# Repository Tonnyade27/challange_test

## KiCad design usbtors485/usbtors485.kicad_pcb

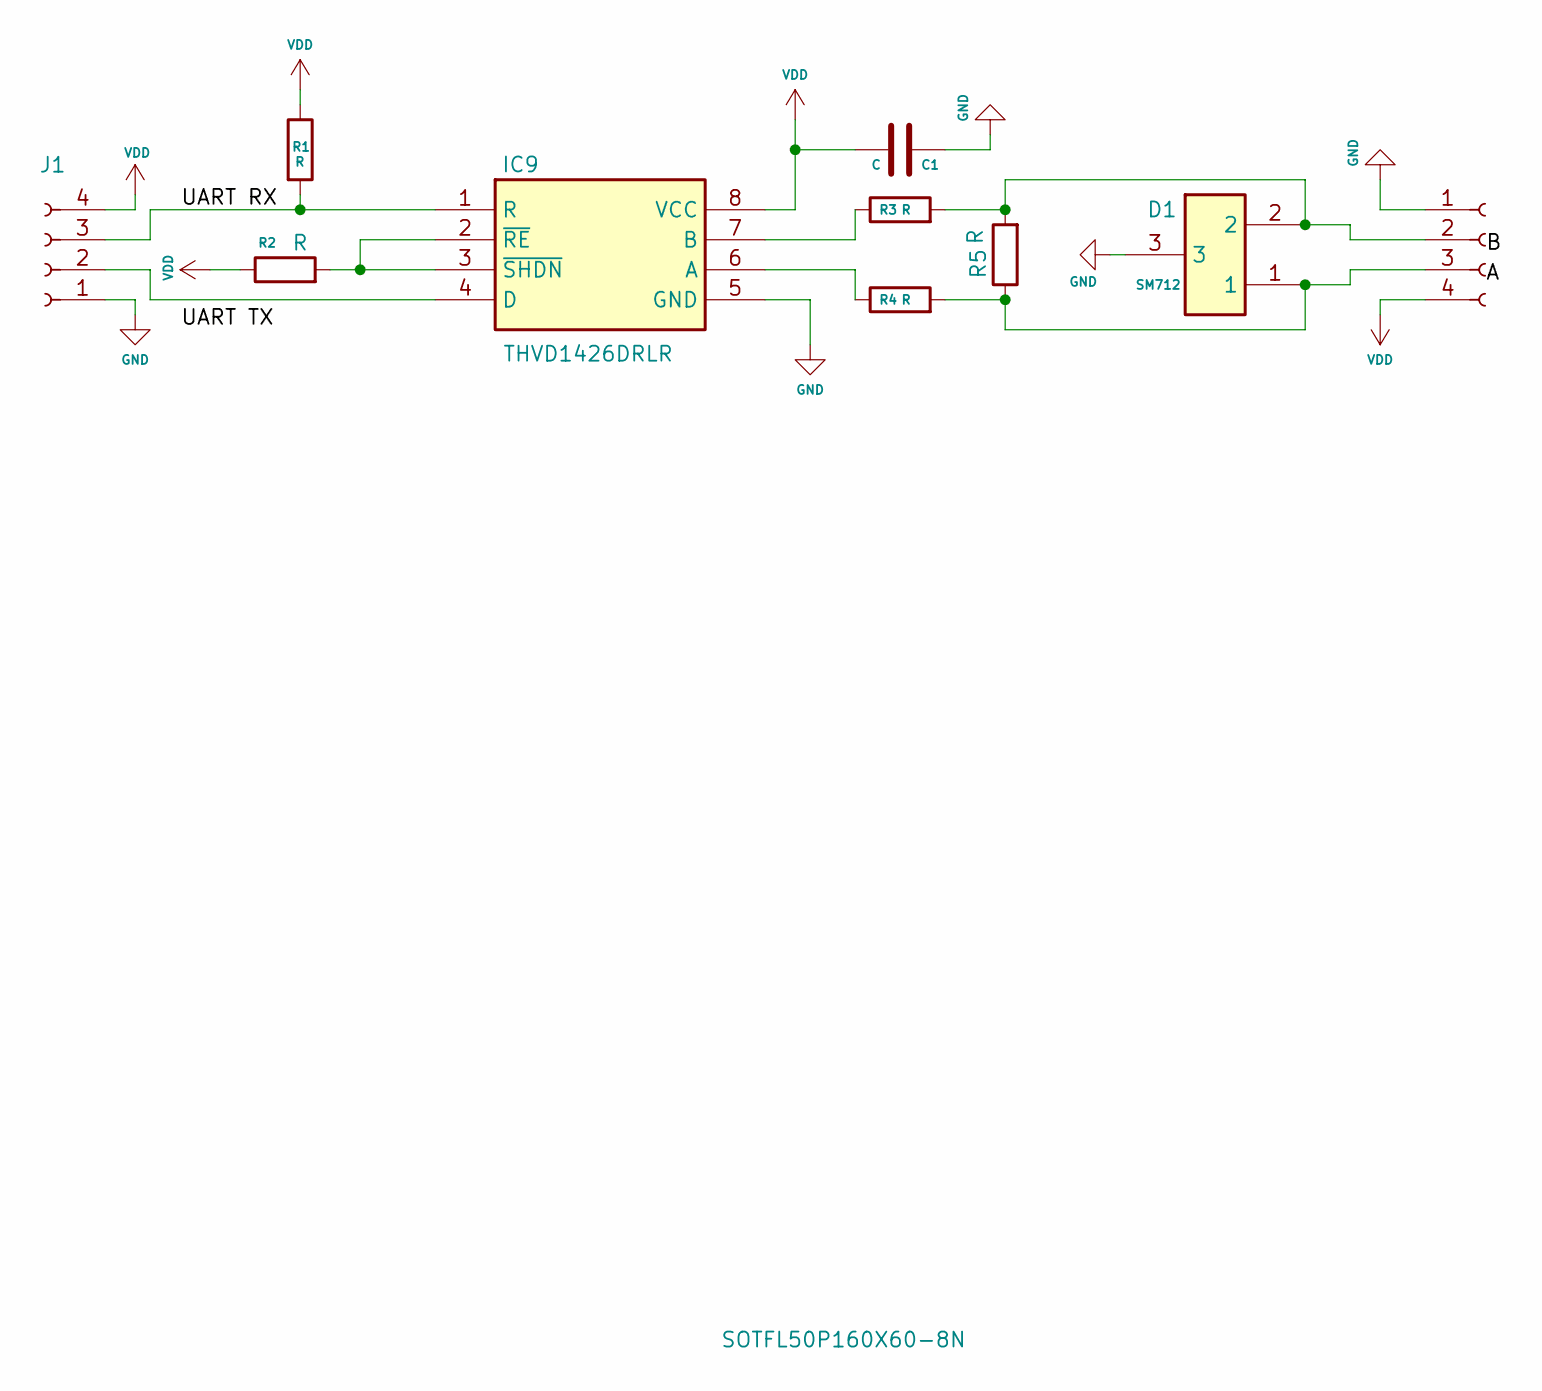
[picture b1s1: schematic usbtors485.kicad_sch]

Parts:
C1: C; C_0603_1608Metric_Pad1.08x0.95mm_HandSolder
D1: SM712; SOT95P230X117-3N; Mouser Part Number 652-CDSOT23-SM712
IC9: THVD1426DRLR; SOTFL50P160X60-8N; Mouser Part Number 595-THVD1426DRLR
J1: FanPinHeader_1x04_P2.54mm_Vertical
J2: Conn_01x04_Socket; FanPinHeader_1x04_P2.54mm_Vertical
R1: R; R_0603_1608Metric
R2, R3, R4, R5: R; R_0603_1608Metric_Pad0.98x0.95mm_HandSolder

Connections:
/UART RX: IC9.1 (R), J1.3, R1.2
GND: C1.2, D1.3, IC9.5 (GND), J1.1, J2.1
unnamed: IC9.6 (A), R4.1
unnamed: IC9.7 (B), R3.1
unnamed: IC9.4 (D), J1.2
unnamed: IC9.2 (~RE), IC9.3 (~SHDN), R2.2
unnamed: D1.2, J2.2, R3.2, R5.2
unnamed: D1.1, J2.3, R4.2, R5.1
VDD: C1.1, IC9.8 (VCC), J1.4, J2.4, R1.1, R2.1

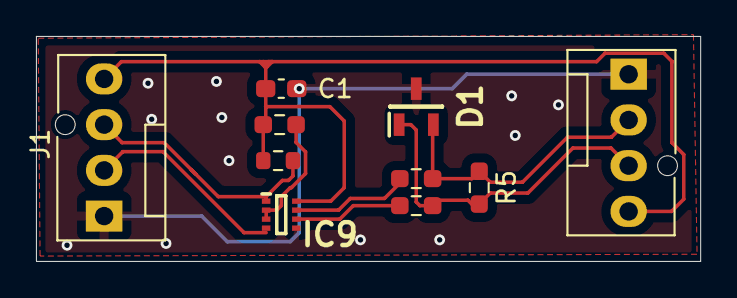
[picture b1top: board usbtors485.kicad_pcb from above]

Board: 2 copper layers, 36.9 x 12.5 mm, 10 parts (0 on the bottom side), 9 nets.

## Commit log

2025-08-07 Schematic project
2025-08-07 update design
2025-08-08 add ground
2025-08-14 fix bug: retry methode to connect wifi and mqtt
